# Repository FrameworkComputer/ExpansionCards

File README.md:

# Expansion Cards
Reference designs and documentation to create Expansion Cards for the Framework Laptop.
The Framework Laptop's Expansion Card system lets you choose exactly the ports you want
and which side you want them on.  We've built USB-C, USB-A, HDMI, DP, MicroSD, and Storage
Expansion Cards, but there is an entire world of other interesting ways to extend the
capabilities of a notebook.  We're releasing CAD to make it easy for you to develop your
own Expansion Cards.

Check out the Expansion Card section of the Framework Community for card ideas, support,
or just to show off what you're working on: https://community.frame.work/c/expansion-cards/developer-program/90

Note that you should build and test
development versions before committing a design based on this CAD to mass production.

## License

Expansion Cards © 2021 by Framework Computer Inc is licensed under CC BY 4.0.
To view a copy of this license, visit http://creativecommons.org/licenses/by/4.0/

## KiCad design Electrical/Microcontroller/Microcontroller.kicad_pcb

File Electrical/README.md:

# Expansion Card Electrical CAD

## License

Expansion Cards © 2021 by Framework Computer Inc is licensed under CC BY 4.0.
To view a copy of this license, visit http://creativecommons.org/licenses/by/4.0/

## Files

 - KiCad_templates - These are templates with the PCB outline and some basic components
   to let you get started with a card design quickly.  The Expansion_Card template
   is designed to be used with the 3D printable enclosures in the Mechanical folder.
   The Expansion_Card_Retrofit template is smaller and designed to fit into the existing
   Expansion Card enclosures like the DP Expansion Card's.  You can copy the folders to
   the default template directory: https://docs.kicad.org/5.0/en/kicad/kicad.html#template_locations
 - Microcontroller - A reference project using a SAMD21 Microcontroller with some pin
   headers broken out.  We've found Preci-Dip 8FM-78-0010-02-146 headers to fit well within the
   size constraints.  **Note:** We've built and done basic validation on an older version
   of this design, but the version currently in this repository is untested.

## Fabrication and Assembly

The templates and reference designs currently in this repository are basic, 2-layer, USB 2.0 designs.
This means the requirements around fabrication and assembly are pretty minimal.  Most PCB makers
and assemblers will be able to handle this.  We've listed a few popular ones below for reference.
Note that these are not necessarily vetted by Framework.

Note that there are pads next to the USB-C plug for manual soldering for additional strength.
You'll have to specify that to your assembler or hand solder that yourself.

PCB Only
 - OSHPark (https://oshpark.com/)

PCB+Assembly
 - Seeed (https://www.seeedstudio.com/fusion_pcb.html)
 - PCBWay (https://www.pcbway.com/pcb-assembly.html)
 - Macrofab (https://macrofab.com/)
 - Circuithub (https://circuithub.com/)

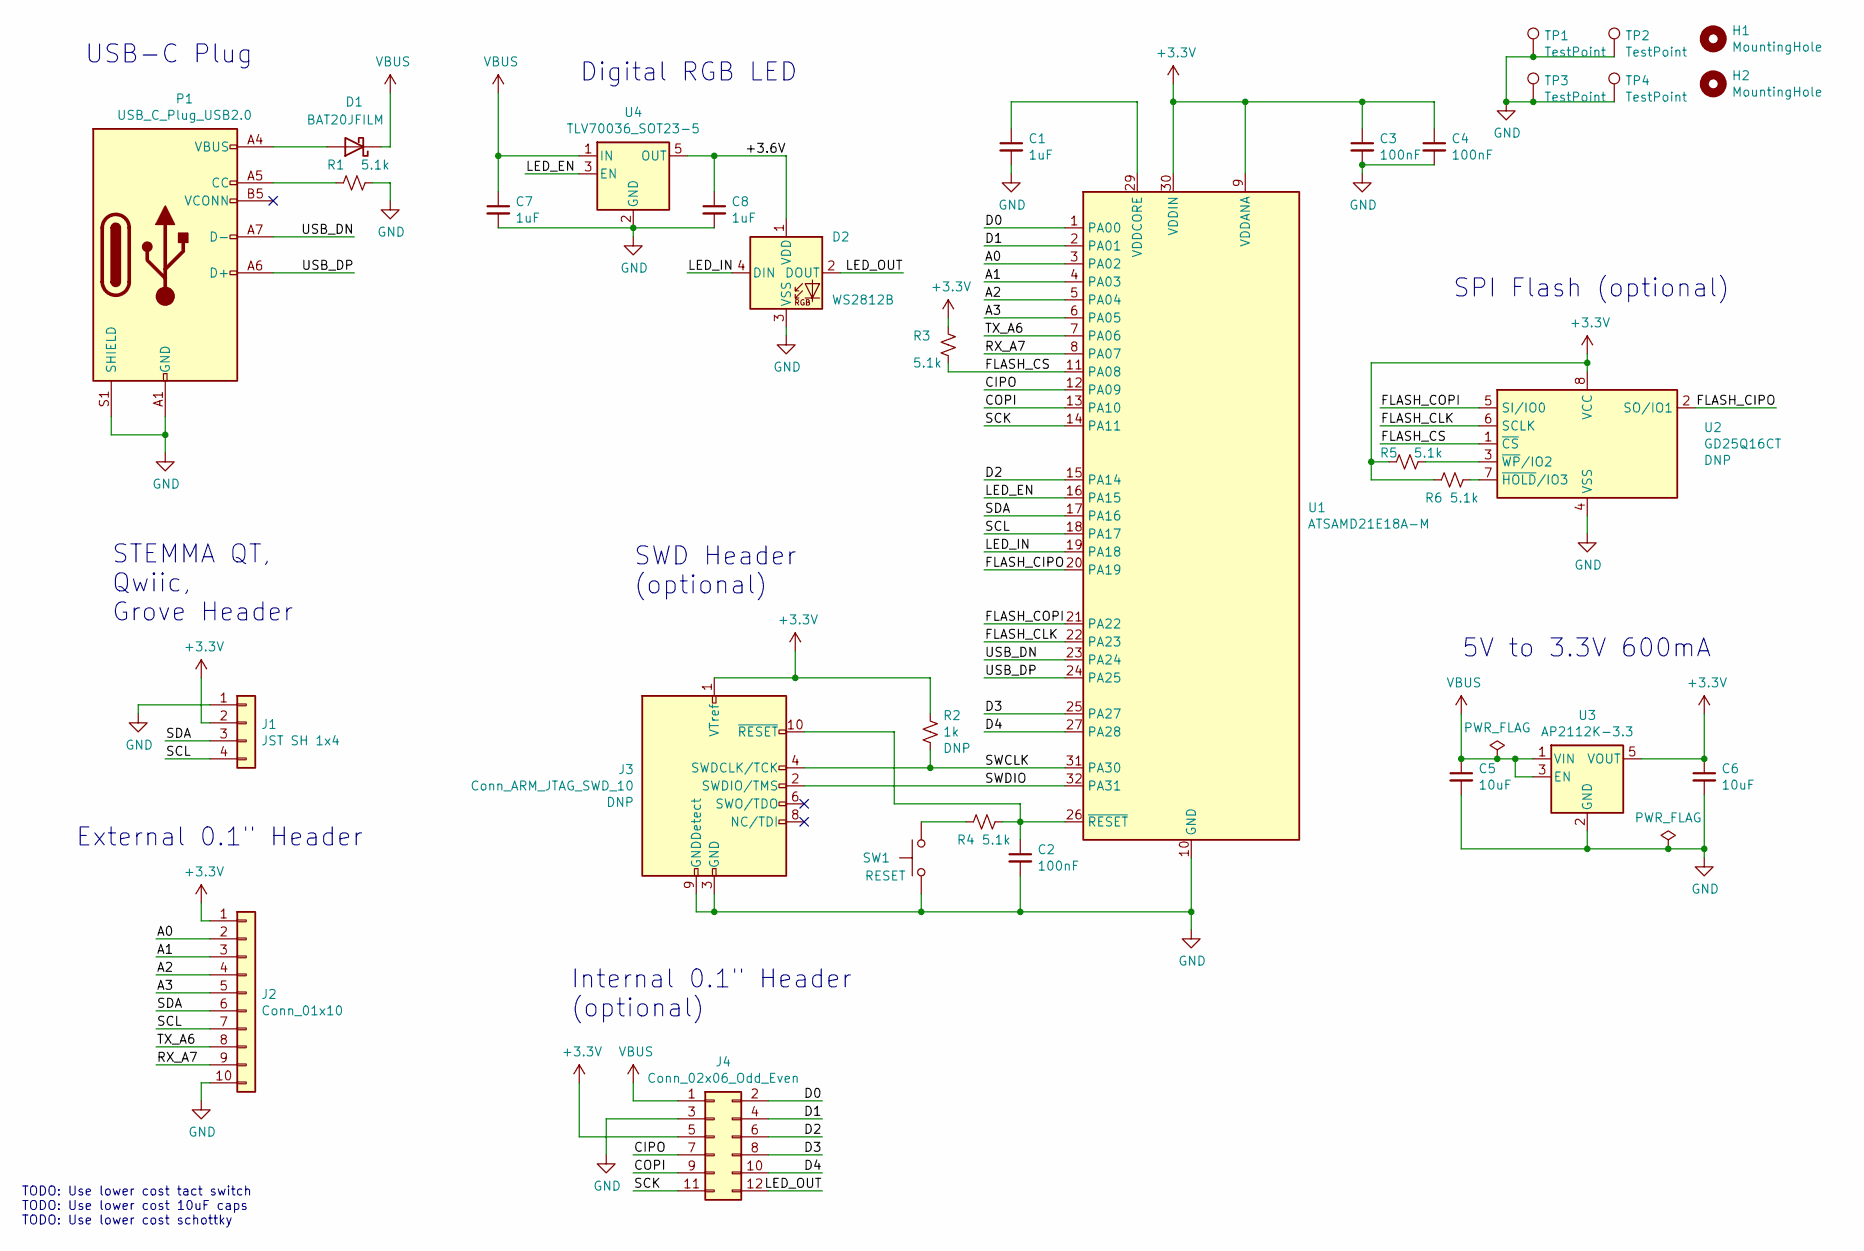
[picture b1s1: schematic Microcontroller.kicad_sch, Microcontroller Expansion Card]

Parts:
C1, C7, C8: 1uF; C_0603_1608Metric
C2, C3, C4: 100nF; C_0603_1608Metric
C5, C6: 10uF; C_0805_2012Metric
D1: BAT20JFILM; D_SOD-323
D2: WS2812B; LED_WS2812B_PLCC4_5.0x5.0mm_P3.2mm
H1, H2: MountingHole; MountingHole_2.2mm_M2
J1: JST SH 1x4; JST_SH_SM04B-SRSS-TB_1x04-1MP_P1.00mm_Horizontal
J2: Conn_01x10; PinSocket_8FM-78-0010-02-146_1x10_P2.54mm_Horizontal_SMD
J3: Conn_ARM_JTAG_SWD_10; PinHeader_2x05_P1.27mm_Vertical_SMD
J4: Conn_02x06_Odd_Even; PinHeader_2x06_P2.54mm_Vertical
P1: USB_C_Plug_USB2.0; USB_C_Plug_Molex_105444
R1, R3, R4, R5, R6: 5.1k; R_0603_1608Metric
R2: 1k; R_0603_1608Metric
SW1: RESET; SW_SPST_B3U-3100P
TP1, TP2, TP3, TP4: TestPoint; TestPoint_Pad_1.5x1.5mm
U1: ATSAMD21E18A-M; QFN-32-1EP_5x5mm_P0.5mm_EP3.6x3.6mm
U2: GD25Q16CT; SOP-8_3.9x4.9mm_P1.27mm
U3: AP2112K-3.3; SOT-23-5
U4: TLV70036_SOT23-5; SOT-23-5

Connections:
+3V3: C3.1, C4.1, C6.1, J1.2, J2.1, J3.1 (VTref), J4.5, R2.1, R3.1, R5.1, R6.1, U1.9 (VDDANA), U1.30 (VDDIN), U2.8 (VCC), U3.5 (VOUT)
/+3.6V: C8.1, D2.1 (VDD), U4.5 (OUT)
/A0: J2.2, U1.3 (PA02)
/A1: J2.3, U1.4 (PA03)
/A2: J2.4, U1.5 (PA04)
/A3: J2.5, U1.6 (PA05)
/CIPO: J4.7, U1.12 (PA09)
/COPI: J4.9, U1.13 (PA10)
/D0: J4.2, U1.1 (PA00)
/D1: J4.4, U1.2 (PA01)
/D2: J4.6, U1.15 (PA14)
/D3: J4.8, U1.25 (PA27)
/D4: J4.10, U1.27 (PA28)
/FLASH_CIPO: U1.20 (PA19), U2.2 (SO/IO1)
/FLASH_CLK: U1.22 (PA23), U2.6 (SCLK)
/FLASH_COPI: U1.21 (PA22), U2.5 (SI/IO0)
/FLASH_CS: R3.2, U1.11 (PA08), U2.1 (~CS)
/LED_EN: U1.16 (PA15), U4.3 (EN)
/LED_IN: D2.4 (DIN), U1.19 (PA18)
/LED_OUT: D2.2 (DOUT), J4.12
/RX_A7: J2.9, U1.8 (PA07)
/SCK: J4.11, U1.14 (PA11)
/SCL: J1.4, J2.7, U1.18 (PA17)
/SDA: J1.3, J2.6, U1.17 (PA16)
/SWCLK: J3.4 (SWDCLK/TCK), R2.2, U1.31 (PA30)
/SWDIO: J3.2 (SWDIO/TMS), U1.32 (PA31)
/TX_A6: J2.8, U1.7 (PA06)
/USB_DN: P1.A7 (D-), U1.23 (PA24)
/USB_DP: P1.A6 (D+), U1.24 (PA25)
GND: C1.2, C2.2, C3.2, C4.2, C5.2, C6.2, C7.2, C8.2, D2.3 (VSS), J1.1, J2.10, J3.3 (GND), J3.5 (GND), J3.9 (GNDDetect), J4.3, P1.A1 (GND), P1.A12 (GND), P1.B1 (GND), P1.B12 (GND), P1.S1 (SHIELD), R1.2, SW1.1, TP1.1, TP2.1, TP3.1, TP4.1, U1.10 (GND), U1.28 (GND), U1.33 (EP), U2.4 (VSS), U3.2 (GND), U4.2 (GND)
unnamed: C1.1, U1.29 (VDDCORE)
unnamed: C2.1, J3.10 (~RESET), R4.2, U1.26 (~RESET)
unnamed: D1.2 (A), P1.A4 (VBUS), P1.A9 (VBUS), P1.B4 (VBUS), P1.B9 (VBUS)
unnamed: P1.A5 (CC), R1.1
unnamed: R4.1, SW1.2
unnamed: R5.2, U2.3 (~WP/IO2)
unnamed: R6.2, U2.7 (~HOLD/IO3)
VBUS: C5.1, C7.1, D1.1 (K), J4.1, U3.1 (VIN), U3.3 (EN), U4.1 (IN)

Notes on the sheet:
STEMMA QT, Qwiic, Grove Header
SWD Header (optional)
SPI Flash (optional)
External 0.1" Header
TODO: Use lower cost tact switch TODO: Use lower cost 10uF caps TODO: Use lower cost schottky
5V to 3.3V 600mA
USB-C Plug
Internal 0.1" Header (optional)
Digital RGB LED

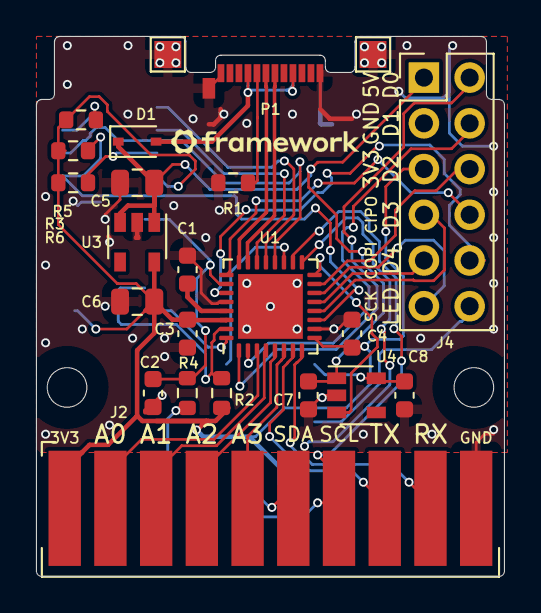
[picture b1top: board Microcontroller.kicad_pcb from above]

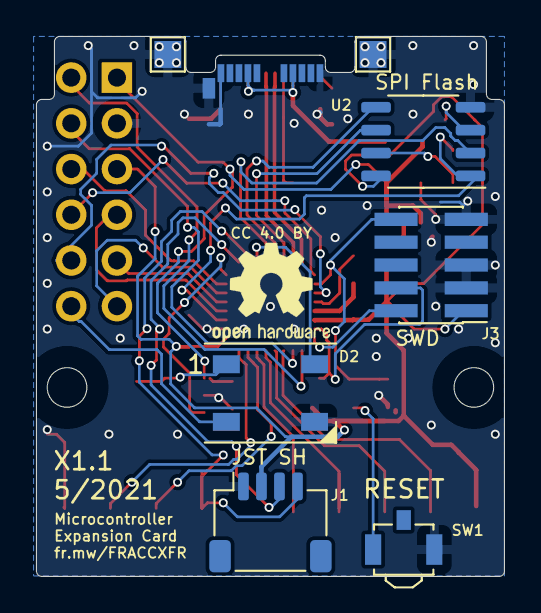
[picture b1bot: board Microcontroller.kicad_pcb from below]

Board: 2 copper layers, 26.0 x 30.0 mm, 32 parts (7 on the bottom side), 38 nets.

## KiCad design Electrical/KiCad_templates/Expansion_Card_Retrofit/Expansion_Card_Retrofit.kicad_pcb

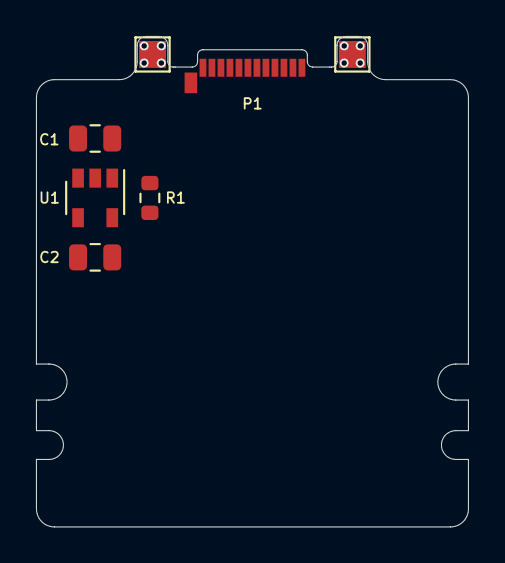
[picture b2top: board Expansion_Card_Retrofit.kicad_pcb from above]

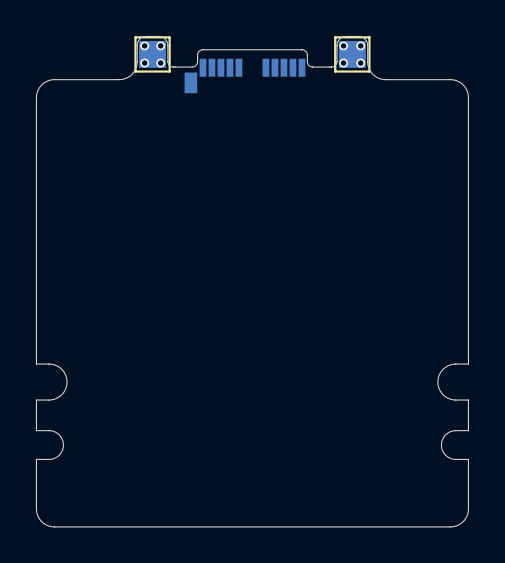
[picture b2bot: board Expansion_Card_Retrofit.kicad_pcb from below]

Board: 2 copper layers, 24.0 x 27.3 mm, 9 parts (2 on the bottom side), 4 nets, no tracks yet.

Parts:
C1, C2: 10uF; C_0805_2012Metric
P1: USB_C_Plug_USB2.0; USB_C_Plug_Molex_105444
R1: 5.1k; R_0603_1608Metric
TP1, TP2, TP3, TP4: TestPoint; TestPoint_Pad_1.5x1.5mm
U1: AP2112K-3.3; SOT-23-5

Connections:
+3V3: C2.1, U1.5
GND: C1.2, C2.2, P1.A1, P1.A12, P1.B1, P1.B12, P1.S1, R1.2, TP1.1, TP2.1, TP3.1, TP4.1, U1.2
unnamed: P1.A5, R1.1
VBUS: C1.1, P1.A4, P1.A9, P1.B4, P1.B9, U1.1, U1.3

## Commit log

2021-05-17 Mechanical CAD
2021-05-17 Add images to Mechanical readme
2021-05-17 Add image
2021-05-18 Add electrical folder and template
2021-05-18 Add Microcontroller reference design
2021-05-18 Add Microcontroller image
2021-05-18 Add supplier examples for electrical
2021-05-18 Switch to the GIF
2021-05-28 Retrofit PCBA
2021-05-28 Update test points
2021-05-29 Add note about retrofit PCB
2021-05-30 Link to community
2021-05-30 Add application form
2021-06-03 Fab drawing updates
2021-06-10 Replace GIF with Microcontroller version
2021-06-10 Switch community URL
2021-06-15 Add a Microcontroller enclosure
2021-08-05 Add ExpansionCard Fusion360 Export
2021-08-05 Add files via upload
    Fix issue, Add Chamfer to Front
2021-08-05 Delete ExpansionCard.f3d
    Remove old F3d file, add new one
2021-08-06 Add files via upload
    Add MicrocontrollerHousing Fusion 360
2022-04-20 Add License
2022-04-20 Rename README to LICENSE
2022-05-14 Raw Links 🠖 Link References
2022-05-14 Added License Badge
2022-05-14 Layout Adjustments
2022-05-14 Formatted Beta Note
2022-05-14 Formatted Description
2022-05-14 Added Quicklinks
2022-05-14 Adjusted Spacing
2022-05-14 Adjusted Style
2022-07-31 Fixed Up Style
2022-07-31 Linke Framework & Added License Alt
2023-02-24 changed documentation of usb-c molex connector with the actual documentation (https://www.molex.com/pdm_docs/ps/1054440001-000.pdf)
2023-02-25 removed temp files
2023-02-25 updated gitignore
2023-03-28 added schematics and projects files
2023-06-14 Fixed designators and clarified footprint of D2.
    I did change the C2 and R4 designators since they were mixed up.
    I also did modify the footprint of D2 to make it more obvious how to orient it since usually pin 1 is marked on the physical package but for that LED it's pin 3.
    Also updated the files to KiCad 7.
2023-09-04 Add pdfs for templates
2023-11-24 Update README.md
    Developer funding program ended.
2024-01-06 Note on 8FM-78-0010-02-146
2024-05-09 Add CLA and CLA workflow, update cla.yml

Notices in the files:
Electrical/KiCad_templates/Expansion_Card_Retrofit/Expansion_Card_Retrofit.kicad_pcb:
This work is licensed under a Creative Commons Attribution 4.0 International License
